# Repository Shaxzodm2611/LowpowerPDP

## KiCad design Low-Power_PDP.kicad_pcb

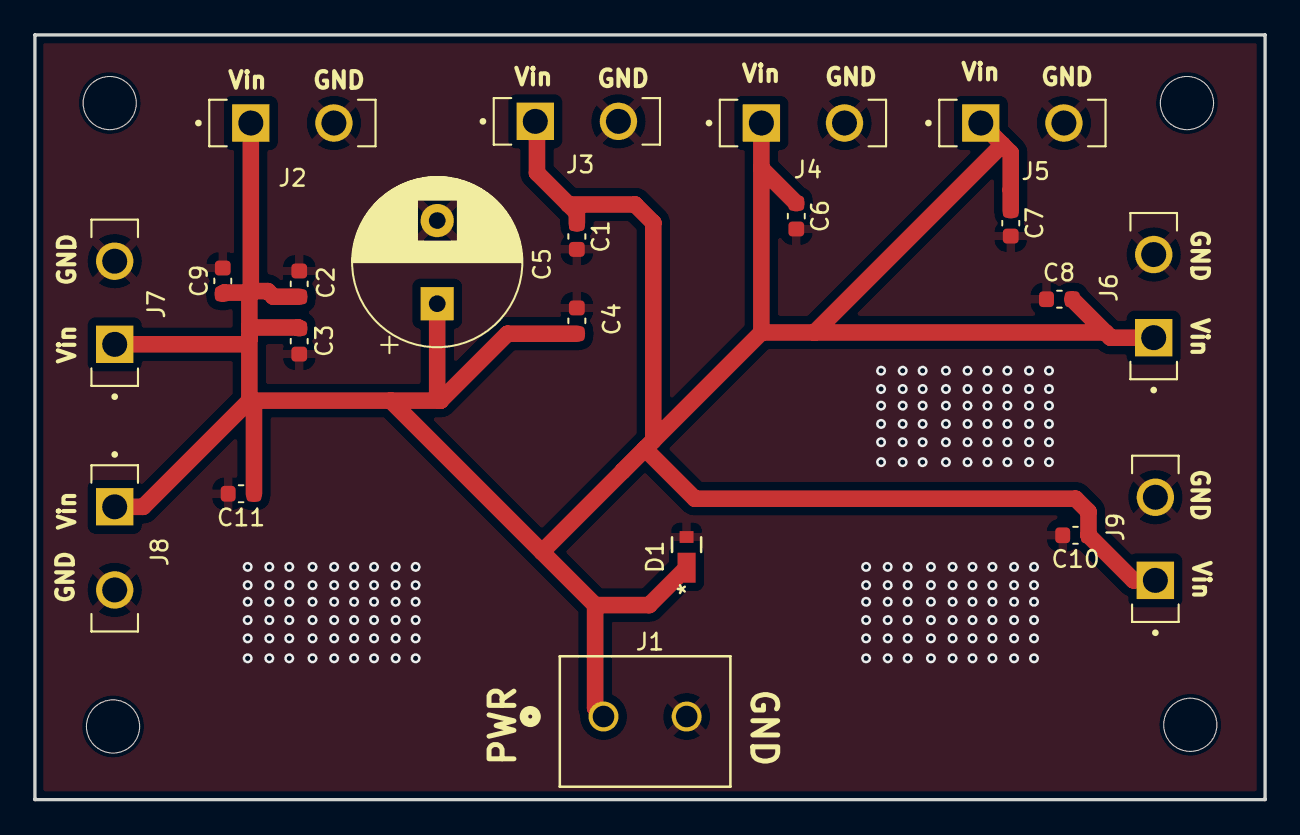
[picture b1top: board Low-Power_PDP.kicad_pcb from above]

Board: 2 copper layers, 74.0 x 46.0 mm, 21 parts (0 on the bottom side), 2 nets.

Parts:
C1, C4, C6, C7, C8, C9, C10, C11: 0.01uF; C_0603_1608Metric
C2: 0.1uF; C_0603_1608Metric
C3: 1uF; C_0603_1608Metric
C5: 10uF; CP_Radial_D10.0mm_P5.00mm
D1: DZ2S051X0L; CLAMPDIODE
J1: Screw_Terminal_01x02; CONN2_710002_WRE
J2, J3, J4, J5, J6, J7, J8, J9: 1933189; PHOENIX_1933189 (2x1 Connector 5mm pitch

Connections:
GND: C1.2, C2.2, C3.2, C4.2, C5.2, C6.2, C7.2, C8.2, C9.2, C10.2, C11.2, D1.2 (A), J1.2, J2.02, J3.02, J4.02, J5.02, J6.02, J7.02, J8.02, J9.02
VCC: C1.1, C2.1, C3.1, C4.1, C5.1, C6.1, C7.1, C8.1, C9.1, C10.1, C11.1, D1.1 (K), J1.1, J2.01, J3.01, J4.01, J5.01, J6.01, J7.01, J8.01, J9.01

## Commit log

2024-08-04 Add files via upload
    Contains the KiCad capture files, PCB design files, footprint and symbol library files, and gerber files which were sent to JLCPCB in order to fabricate the board. The board was ordered and realized,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
    NOTE:
    If one is to copy this design, a resistor must be added in series with the TVS diode in order not to burn the diode once the breakdown voltage has been reached.
